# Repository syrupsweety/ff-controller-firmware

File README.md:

# Force feedback manipulator firmware

This is a custom force feedback controller firmware for the RP2350 microcontroller with ROS2 integration.

## Hardware features

- Microcontroller: RP2350

- Input sensors:

  - Piezo sensor (12-bit ADC) for force/vibration detection
  - Analog joystick (X/Y axes, 12-bit ADC)
  - 3 digital buttons (active-low with pull-ups)

- Actuator interface: UART (9600 baud) for motor control

- Communication: I2C slave interface (400kHz Fast Mode, address 0x08)

## Software Architecture

- Firmware: Bare-metal C using Pico SDK

  - ADC reader with moving average filtering
  - I2C slave with IRQ-based TX/RX handling
  - UART motor command protocol (framed packets)

- ROS2 driver: C++ node running on host machine

  - Polls controller via I2C at configurable rate (default 50Hz)
  - Publishes sensor data to `/controller/input` topic
  - Subscribes to `/controller/motor_command` for actuator commands

## Protocol

- I2C Read: 8 bytes (controller data + XOR checksum)
- I2C Write: 4 bytes [START, speed, dir+enable, END]

## Build

- Firmware compiles to .uf2 for drag-and-drop flashing
- ROS2 packages build with colcon
- Automated build/flash scripts included

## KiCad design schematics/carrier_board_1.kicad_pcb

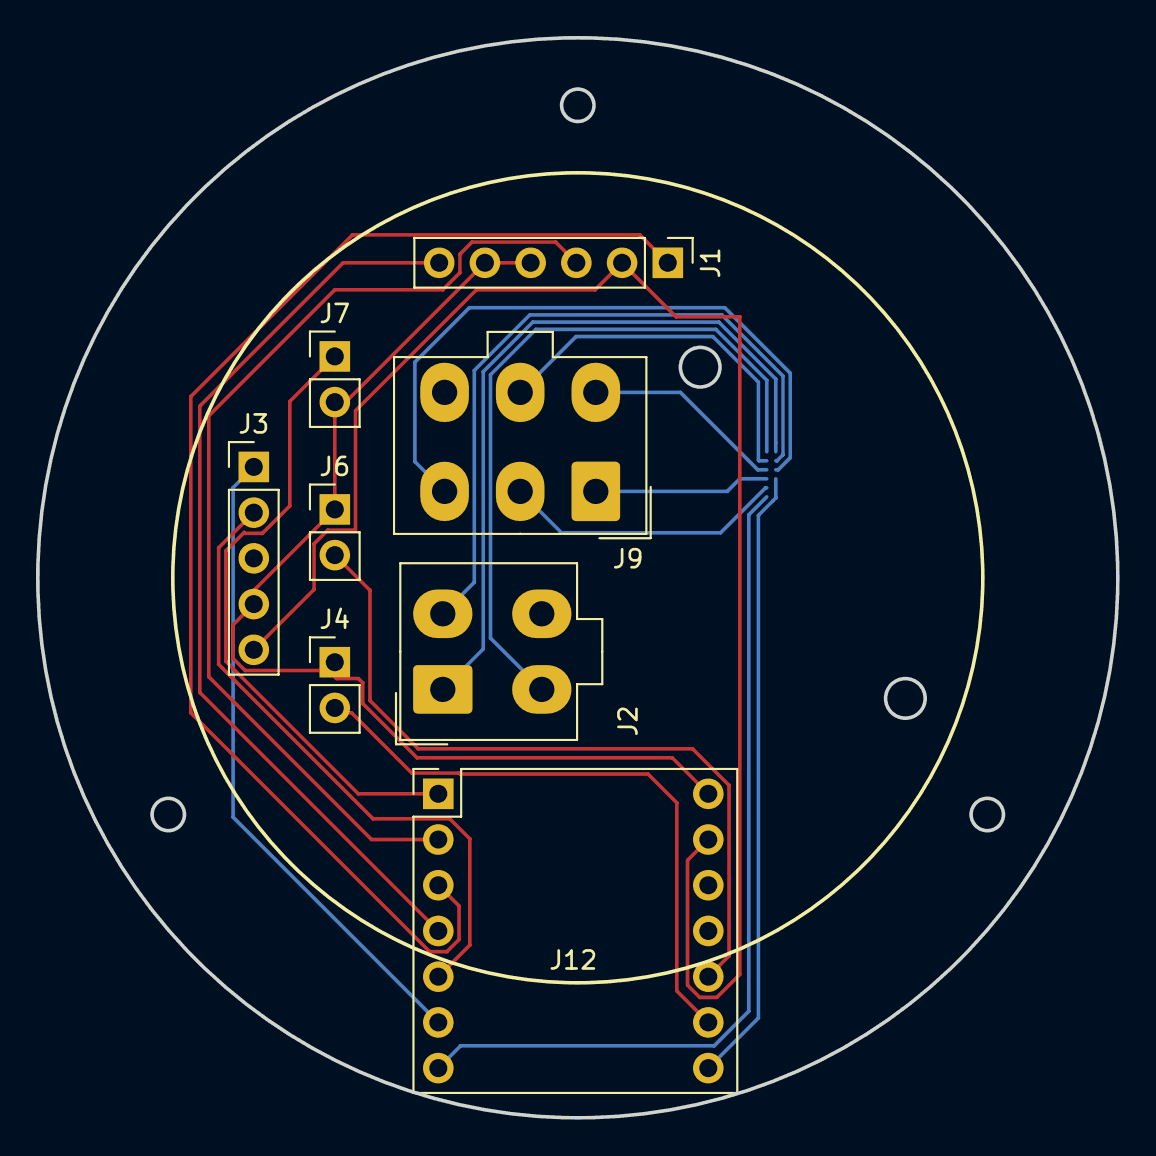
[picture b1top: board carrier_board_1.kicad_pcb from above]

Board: 2 copper layers, 60.0 x 60.0 mm, 8 parts (0 on the bottom side), 10 nets.

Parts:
J1: joystick; PinHeader_1x06_P2.54mm_Vertical
J2: 4 pin BLDC; Molex_Mini-Fit_Jr_5566-04A_2x02_P4.20mm_Vertical
J3: econ; PinHeader_1x05_P2.54mm_Vertical
J4: button1; PinHeader_1x02_P2.54mm_Vertical
J6: button0; PinHeader_1x02_P2.54mm_Vertical
J7: piezo; PinHeader_1x02_P2.54mm_Vertical
J9: 6 pin BLDC; Molex_Mini-Fit_Jr_5566-06A_2x03_P4.20mm_Vertical
J12: XIAO RP2350; PinHeader_2x07_P2.54mm_Vertical

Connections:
unnamed: J1.LR (1), J12.A2 (5)
unnamed: J1.GND (2), J3.GND (4), J12.GND (4)
unnamed: J1.UD (3), J12.A1 (3)
unnamed: J1.B0 (5), J1.VCC (4), J3.5v (5), J4.1, J6.1, J7.2, J12.5V (2)
unnamed: J1.B1 (6), J12.D3 (7)
unnamed: J7.1, J12.A0 (1)
unnamed: J3.SDA (2), J12.SDA1 (9)
unnamed: J6.2, J12.D9 (10)
unnamed: J3.SCL (1), J12.SCL1 (11)
unnamed: J4.2, J12.D8 (12)
